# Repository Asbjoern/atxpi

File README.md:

# atxpi #

Raspberry Pi ATX power controller using the [teensy](http://www.pjrc.com/teensy/) microcontroller. The atxpi emulates ACPI behavior, handling ATX power supply states, power / reset buttons, and LEDs.

---

 - [Parts List](#parts-list)
 - [Power / Reset Buttons](#buttons)
 - [GPIO Pins](#gpio)
 - [RPI Power Scripts Installation](#power-scripts)
	- [Arch](#power-scripts-arch)
	- [Raspbian](#power-scripts-raspbian)
 - [Schematic](#schematic)

---

<h2 id="parts-list">Parts List</h2>

 - [Teensy 2.0](http://www.pjrc.com/store/teensy.html)
 - [Logic Level Converter](https://www.sparkfun.com/products/11978)
 - [ATX Connector Breakout Board](https://www.sparkfun.com/products/9558)
 - [ATX Power Supply Connector](https://www.sparkfun.com/products/9498)

---

<h2 id="buttons">Power / Reset Buttons</h2>

 - Power state 0:
	- Power button pressed: power on
	- Reset button pressed: do nothing

 - Power state 1:
	- Power button pressed for 1 second: Tell RPI to shutdown by setting GPIO pin 23 HIGH
	- Power button pressed for 5 seconds: Force power off
	- Reset button pressed for 1 second: Force power cycle

---

<h2 id="gpio">GPIO Pins</h2>

The RPI will monitor GPIO 23 and shutdown if it is set to HIGH. After the RPI boots it will set GPIO 24 HIGH, telling the teensy that the RPI is up. When GPIO 24 goes from HIGH to LOW the teensy will wait 5 seconds then cut power, unless GPIO 25 is HIGH. GPIO 25 is set to HIGH when the RPI is rebooting, preventing the teensy from cutting power when GPIO 24 changes from HIGH to LOW.

---

<h2 id="power-scripts">RPI Power Scripts Installation</h2>

<h3 id="power-scripts-arch">Arch</h3>

Log into the RPI and become root. You will need to install git and WiringPi:

	[root@alarmpi ~]$ pacman -Sy git wiringpi

Next, clone the repo and copy required files.

	[root@alarmpi ~]$ git clone https://github.com/steelcaverobotics/atxpi.git
	[root@alarmpi ~]$ mkdir /opt/atxpi
	[root@alarmpi ~]$ cp atxpi/rpi_power_scripts/*.sh /opt/atxpi/
	[root@alarmpi ~]$ chmod 755 /opt/atxpi/*.sh
	[root@alarmpi ~]$ cp atxpi/service_files/arch/*.service /usr/lib/systemd/system/

Then enable the services, skipping `atxpi-gpio-shutdown.service` if you don't want the RPI to shutdown when the power button is pressed.

	[root@alarmpi ~]$ systemctl enable atxpi-gpio-boot.service
	[root@alarmpi ~]$ systemctl enable atxpi-gpio-reboot.service
	[root@alarmpi ~]$ systemctl enable atxpi-gpio-shutdown.service

Finally, start the services. Do not start `atxpi-gpio-reboot.service`, as this will be started when the RPI is rebooting.

	[root@alarmpi ~]$ systemctl start atxpi-gpio-boot.service
	[root@alarmpi ~]$ systemctl start atxpi-gpio-shutdown.service

<h3 id="power-scripts-raspbian">Raspbian</h3>

Log into the RPI and become root. You will need to install git and WiringPi:

	root@raspberrypi:~# apt-get install git-core
	root@raspberrypi:~# git clone git://git.drogon.net/wiringPi
	root@raspberrypi:~# cd wiringPi/
	root@raspberrypi:~# ./build

Next, clone the repo and copy required files.

	root@raspberrypi:~# git clone https://github.com/steelcaverobotics/atxpi.git
	root@raspberrypi:~# mkdir /opt/atxpi
	root@raspberrypi:~# cp atxpi/rpi_power_scripts/*.sh /opt/atxpi/
	root@raspberrypi:~# chmod 755 /opt/atxpi/*.sh
	root@raspberrypi:~# cp atxpi/service_files/raspbian/* /etc/init.d/
	root@raspberrypi:~# chmod 755 /etc/init.d/atxpi-gpio-*

Then enable the services, skipping `atxpi-gpio-shutdown` if you don't want the RPI to shutdown when the power button is pressed.

	root@raspberrypi:~# update-rc.d atxpi-gpio-boot defaults
	root@raspberrypi:~# update-rc.d atxpi-gpio-reboot defaults
	root@raspberrypi:~# update-rc.d atxpi-gpio-shutdown defaults

Finally, start the services.

	root@raspberrypi:~# /etc/init.d/atxpi-gpio-boot start
	root@raspberrypi:~# /etc/init.d/atxpi-gpio-shutdown start

---

<h2 id="schematic">Schematic</h2>

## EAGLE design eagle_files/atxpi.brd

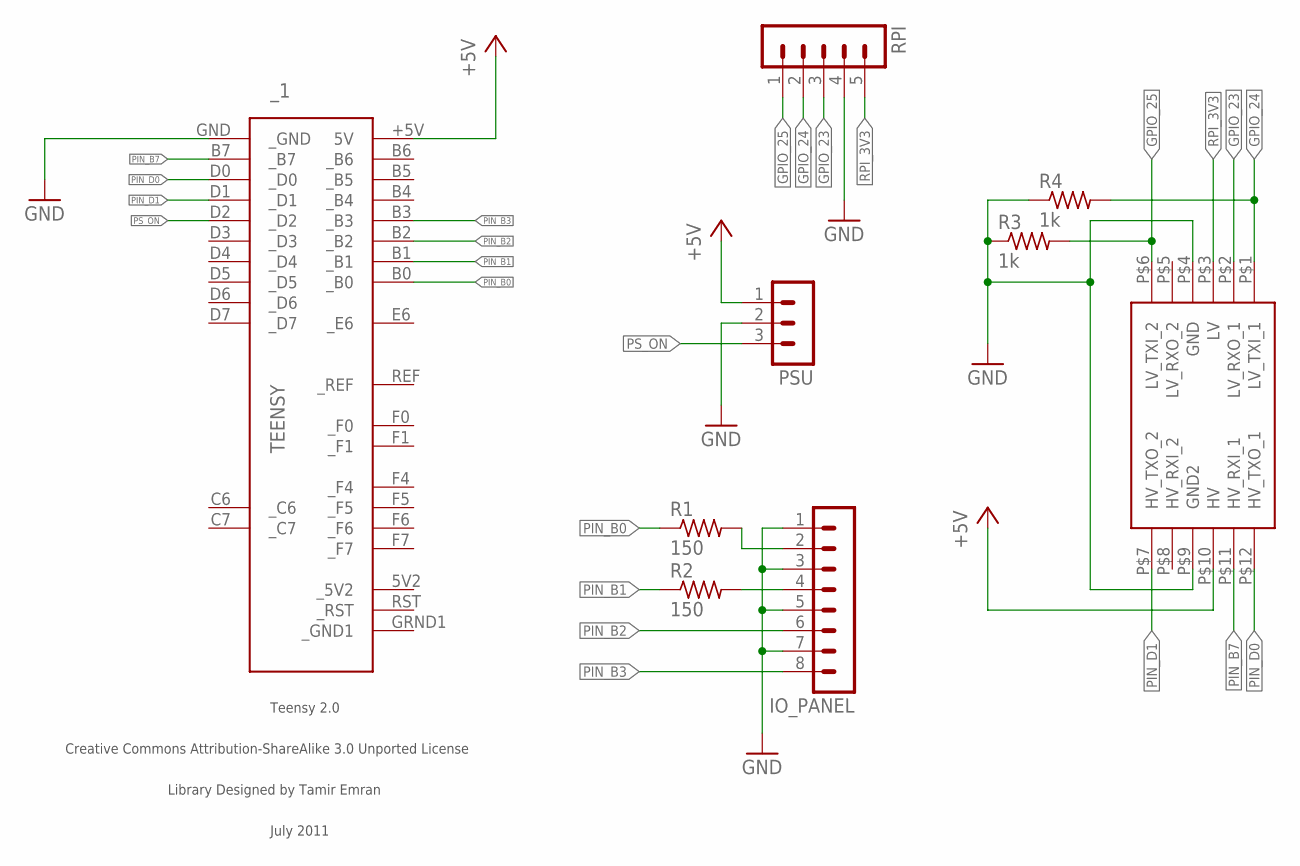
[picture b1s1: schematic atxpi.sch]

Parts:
IO_PANEL: MA08-1
PSU: MA03-1
R1, R2: 150; 0309/12
R3, R4: 1k; 0309/12
RPI: MA05-1
U$1: LOGIC_LEVEL_CONVERTER
_1: TEENSY

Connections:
+5V: PSU.1, U$1.P$10 (HV), _1.+5V (5V)
GND: IO_PANEL.1, IO_PANEL.3, IO_PANEL.5, IO_PANEL.7, PSU.2, R3.1, R4.1, RPI.4, U$1.P$4 (GND), U$1.P$9 (GND2), _1.GND (_GND)
GPIO_23: RPI.3, U$1.P$2 (LV_RXO_1)
GPIO_24: R4.2, RPI.2, U$1.P$1 (LV_TXI_1)
GPIO_25: R3.2, RPI.1, U$1.P$6 (LV_TXI_2)
HDD_LED: IO_PANEL.4, R2.2
unnamed: IO_PANEL.2, R1.2
PIN_B0: R1.1, _1.B0 (_B0)
PIN_B1: R2.1, _1.B1 (_B1)
PIN_B2: IO_PANEL.6, _1.B2 (_B2)
PIN_B3: IO_PANEL.8, _1.B3 (_B3)
PIN_B7: U$1.P$11 (HV_RXI_1), _1.B7 (_B7)
PIN_D0: U$1.P$12 (HV_TXO_1), _1.D0 (_D0)
PIN_D1: U$1.P$7 (HV_TXO_2), _1.D1 (_D1)
PS_ON: PSU.3, _1.D2 (_D2)
RPI_3V3: RPI.5, U$1.P$3 (LV)

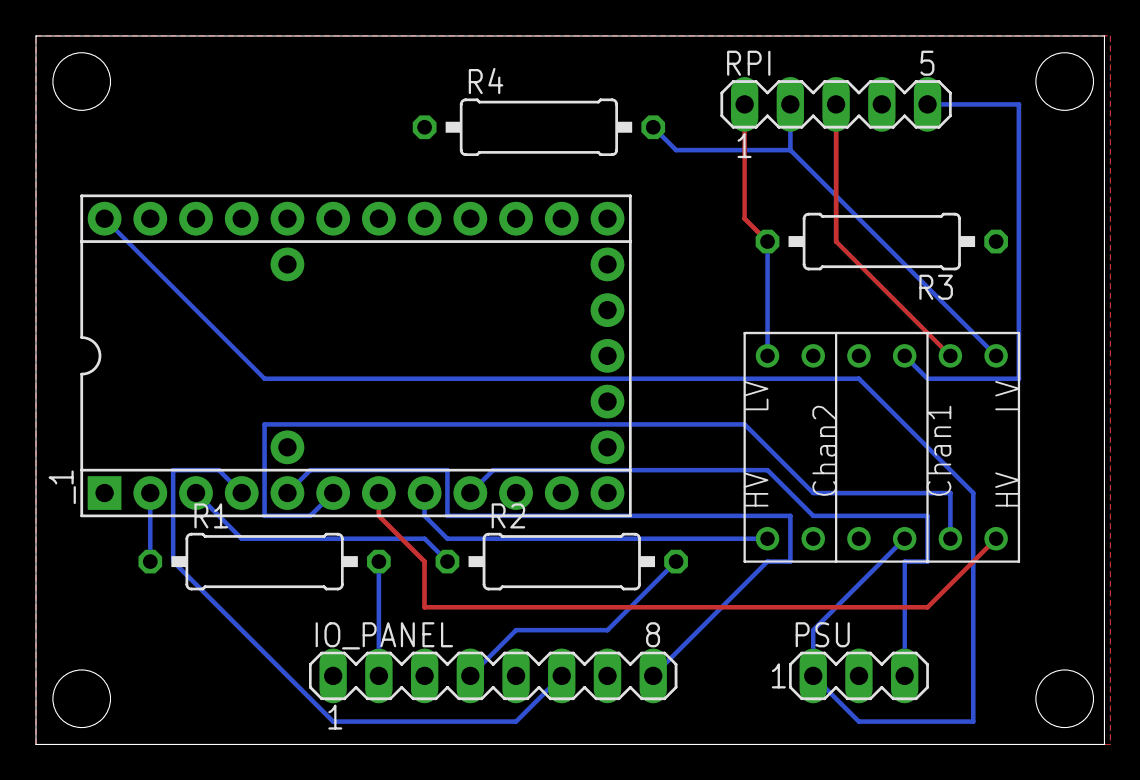
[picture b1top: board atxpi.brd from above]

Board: 2 copper layers, 59.4 x 39.4 mm, 9 parts (0 on the bottom side), 16 nets.

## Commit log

2013-09-16 started atxpi code for the teensy2.0 microcontroller
2013-09-16 changed file type
2013-09-18 implemented power and reset button functionality
2013-09-24 implemented rpi gpio functionality and added debugging
2013-09-27 turned off debug, added hdd led, and changed pin numbers
2013-09-28 changed forced shutdown and reset times
2013-11-11 add atxpi eagle schematic
2013-11-11 update and fix atxpi schematic
2013-11-27 add atxpi schematic png
2013-11-27 add rpi power scripts
2013-11-27 fix gpio pin number in reboot.sh
2013-11-28 add serial debug control
2013-11-28 add arch service files and update README.md
2013-11-28 add raspbian init scripts and update README.md
2014-02-11 add atxpi board
2014-03-21 GPLv3
2015-05-08 Replaced Teensy/Eagle hardware with ATMEGA328 PCB mounted design
2015-05-08 Swithed pins to new design and replaced Bounce with Bounce2 library

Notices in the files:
parts and their libraries:
teensy: Licensed Under Creative Commons
teensy: Creative Commons Attribution-ShareAlike 3.0 Unported License
teensy: Licensed Under Creative Commons Attribution-ShareAlike 3.0 Unported (CC BY-SA 3.0)
